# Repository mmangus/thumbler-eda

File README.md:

# thumbler-eda
EDA files for split keyboard with clicky encoder and thumb pointer

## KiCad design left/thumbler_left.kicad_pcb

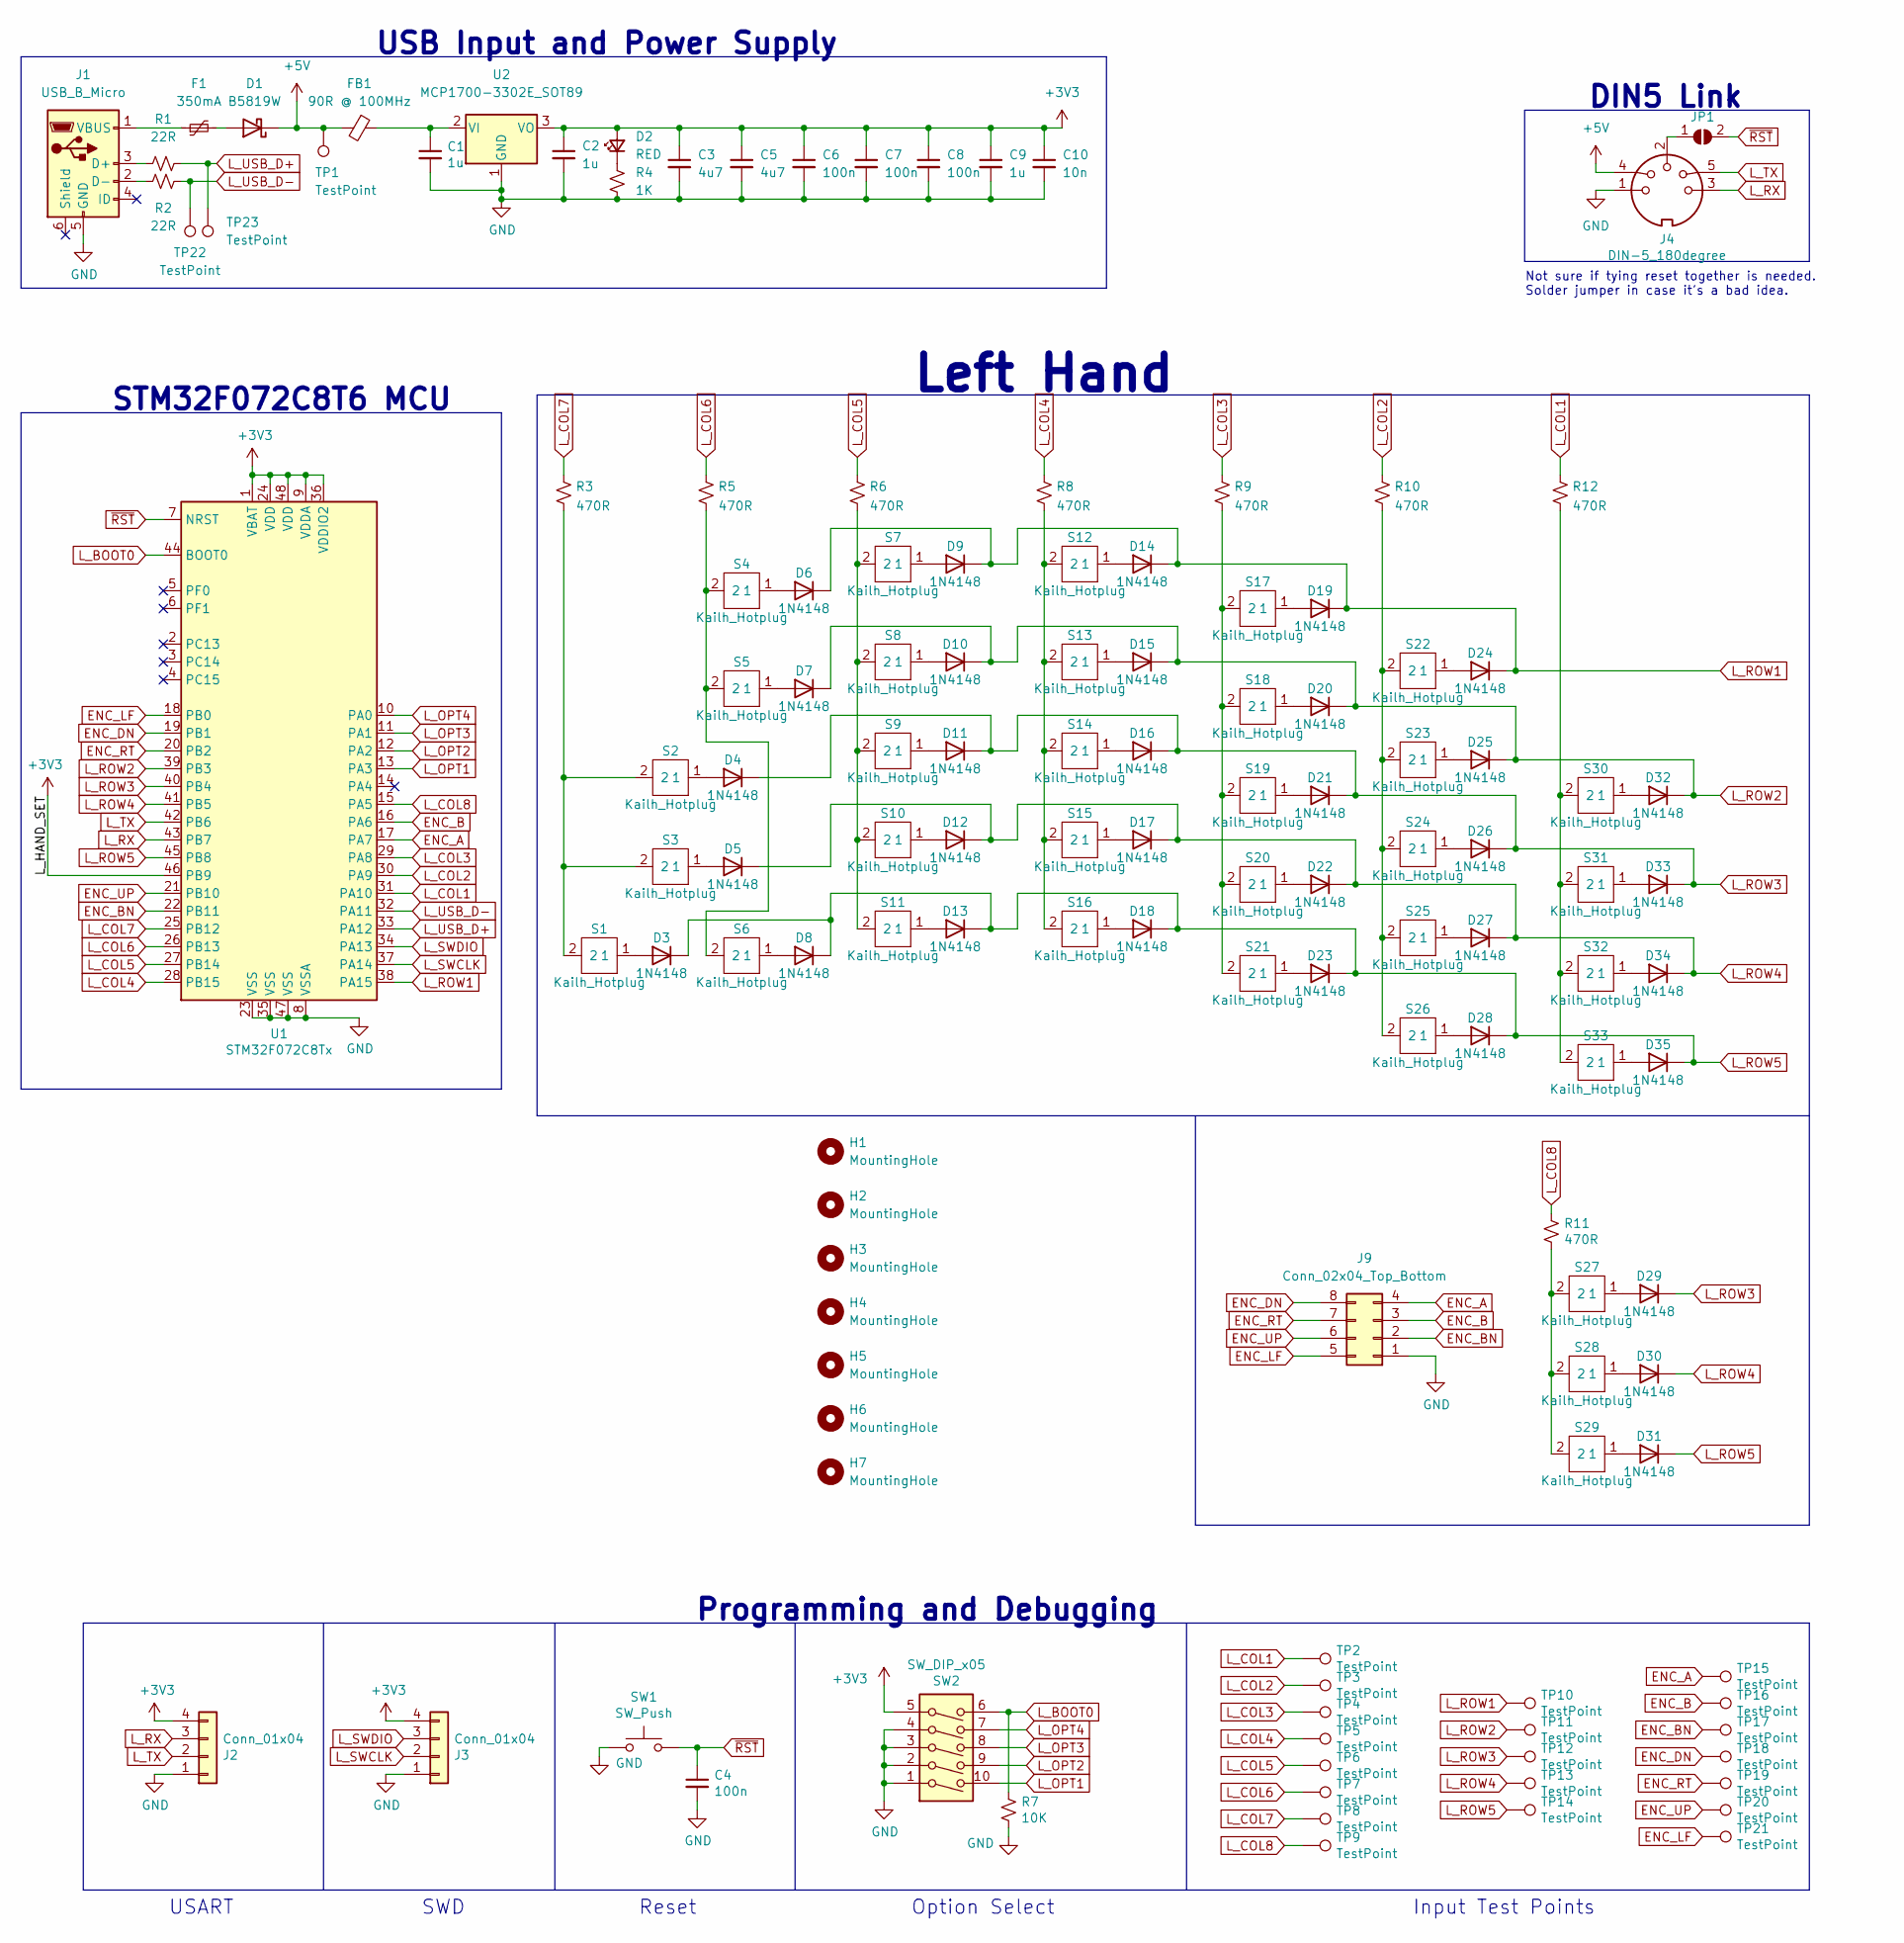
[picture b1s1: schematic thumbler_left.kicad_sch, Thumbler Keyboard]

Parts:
C1, C2: 1u; C_0805_2012Metric_Pad1.18x1.45mm_HandSolder
C3, C5: 4u7; C_0603_1608Metric_Pad1.08x0.95mm_HandSolder
C4: 100n; C_0805_2012Metric_Pad1.18x1.45mm_HandSolder
C6, C7, C8: 100n; C_0603_1608Metric_Pad1.08x0.95mm_HandSolder
C9: 1u; C_0603_1608Metric_Pad1.08x0.95mm_HandSolder
C10: 10n; C_0603_1608Metric_Pad1.08x0.95mm_HandSolder
D1: B5819W; D_SOD-123
D2: RED; LED_1206_3216Metric_Pad1.42x1.75mm_HandSolder
D3, D4, D5, D6, D7, D8, D9, D10, D11, D12, D13, D14, D15, D16, D17, D18, D19, D20, D21, D22, D23, D24, D25, D26, D27, D28, D29, D30, D31, D32, D33, D34, D35: 1N4148; D_DO-35_SOD27_P7.62mm_Horizontal
F1: 350mA; R_1812_4532Metric_Pad1.30x3.40mm_HandSolder
FB1: 90R @ 100MHz; L_0805_2012Metric_Pad1.15x1.40mm_HandSolder
H1, H2, H3, H4, H5, H6, H7: MountingHole; MountingHole_3.2mm_M3
J1: USB_B_Micro; USB_Micro-B_HRO_U-F-M5SS-W-1
J2, J3: Conn_01x04; PinHeader_2x02_P2.54mm_Vertical
J4: DIN-5_180degree; DIN5_180_CP-2350
J9: Conn_02x04_Top_Bottom; PinHeader_2x04_P2.54mm_Vertical
JP1: SolderJumper_2_Open; SolderJumper-2_P1.3mm_Open_TrianglePad1.0x1.5mm
R1, R2: 22R; R_0805_2012Metric_Pad1.20x1.40mm_HandSolder
R3, R5, R6, R8, R9, R10, R11, R12: 470R; R_0805_2012Metric_Pad1.20x1.40mm_HandSolder
R4: 1K; R_0805_2012Metric_Pad1.20x1.40mm_HandSolder
R7: 10K; R_0805_2012Metric_Pad1.20x1.40mm_HandSolder
S1, S2, S3, S4, S5, S6, S7, S8, S9, S10, S11, S12, S13, S14, S15, S16, S17, S18, S19, S20, S21, S22, S23, S24, S25, S26, S27, S28, S29, S30, S31, S32, S33: Kailh_Hotplug; Kailh_socket_MX_platemount
SW1: SW_Push; SW_PUSH-12mm
SW2: SW_DIP_x05; SW_DIP_SPSTx05_Slide_9.78x14.88mm_W7.62mm_P2.54mm
TP1, TP2, TP3, TP4, TP5, TP6, TP7, TP8, TP9, TP10, TP11, TP12, TP13, TP14, TP15, TP16, TP17, TP18, TP19, TP20, TP21, TP22, TP23: TestPoint; TestPoint_Pad_D2.0mm
U1: STM32F072C8Tx; LQFP-48_7x7mm_P0.5mm
U2: MCP1700-3302E_SOT89; SOT-89-3

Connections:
+3V3: C2.1, C3.1, C5.1, C6.1, C7.1, C8.1, C9.1, C10.1, D2.2 (A), J2.4, J3.4, SW2.5, U1.1 (VBAT), U1.9 (VDDA), U1.24 (VDD), U1.36 (VDDIO2), U1.46 (PB9), U1.48 (VDD), U2.3 (VO)
+5V: D1.1 (K), FB1.2, J4.4, TP1.1
ENC_A: J9.4, TP15.1, U1.17 (PA7)
ENC_B: J9.3, TP16.1, U1.16 (PA6)
ENC_BN: J9.2, TP17.1, U1.22 (PB11)
ENC_DN: J9.8, TP18.1, U1.19 (PB1)
ENC_LF: J9.5, TP21.1, U1.18 (PB0)
ENC_RT: J9.7, TP19.1, U1.20 (PB2)
ENC_UP: J9.6, TP20.1, U1.21 (PB10)
GND: C1.2, C2.2, C3.2, C4.2, C5.2, C6.2, C7.2, C8.2, C9.2, C10.2, J1.5 (GND), J2.1, J3.1, J4.1, J9.1, R4.2, R7.2, SW1.1, SW2.1, SW2.2, SW2.3, SW2.4, U1.8 (VSSA), U1.23 (VSS), U1.35 (VSS), U1.47 (VSS), U2.1 (GND)
L_BOOT0: R7.1, SW2.6, U1.44 (BOOT0)
L_COL1: R12.1, TP2.1, U1.31 (PA10)
L_COL2: R10.1, TP3.1, U1.30 (PA9)
L_COL3: R9.1, TP4.1, U1.29 (PA8)
L_COL4: R8.1, TP5.1, U1.28 (PB15)
L_COL5: R6.1, TP6.1, U1.27 (PB14)
L_COL6: R5.1, TP7.1, U1.26 (PB13)
L_COL7: R3.1, TP8.1, U1.25 (PB12)
L_COL8: R11.1, TP9.1, U1.15 (PA5)
L_OPT1: SW2.10, U1.13 (PA3)
L_OPT2: SW2.9, U1.12 (PA2)
L_OPT3: SW2.8, U1.11 (PA1)
L_OPT4: SW2.7, U1.10 (PA0)
L_ROW1: D6.1 (K), D9.1 (K), D14.1 (K), D19.1 (K), D24.1 (K), TP10.1, U1.38 (PA15)
L_ROW2: D7.1 (K), D10.1 (K), D15.1 (K), D20.1 (K), D25.1 (K), D32.1 (K), TP11.1, U1.39 (PB3)
L_ROW3: D4.1 (K), D11.1 (K), D16.1 (K), D21.1 (K), D26.1 (K), D29.1 (K), D33.1 (K), TP12.1, U1.40 (PB4)
L_ROW4: D5.1 (K), D12.1 (K), D17.1 (K), D22.1 (K), D27.1 (K), D30.1 (K), D34.1 (K), TP13.1, U1.41 (PB5)
L_ROW5: D3.1 (K), D8.1 (K), D13.1 (K), D18.1 (K), D23.1 (K), D28.1 (K), D31.1 (K), D35.1 (K), TP14.1, U1.45 (PB8)
L_RX: J2.3, J4.3, U1.43 (PB7)
L_SWCLK: J3.2, U1.37 (PA14)
L_SWDIO: J3.3, U1.34 (PA13)
L_TX: J2.2, J4.5, U1.42 (PB6)
L_USB_D+: R1.1, TP23.1, U1.33 (PA12)
L_USB_D-: R2.2, TP22.1, U1.32 (PA11)
unnamed: C1.1, FB1.1, U2.2 (VI)
unnamed: D1.2 (A), F1.2
unnamed: D2.1 (K), R4.1
unnamed: D3.2 (A), S1.1
unnamed: D4.2 (A), S2.1
unnamed: D5.2 (A), S3.1
unnamed: D6.2 (A), S4.1
unnamed: D7.2 (A), S5.1
unnamed: D8.2 (A), S6.1
unnamed: D9.2 (A), S7.1
unnamed: D10.2 (A), S8.1
unnamed: D11.2 (A), S9.1
unnamed: D12.2 (A), S10.1
unnamed: D13.2 (A), S11.1
unnamed: D14.2 (A), S12.1
unnamed: D15.2 (A), S13.1
unnamed: D16.2 (A), S14.1
unnamed: D17.2 (A), S15.1
unnamed: D18.2 (A), S16.1
unnamed: D19.2 (A), S17.1
unnamed: D20.2 (A), S18.1
unnamed: D21.2 (A), S19.1
unnamed: D22.2 (A), S20.1
unnamed: D23.2 (A), S21.1
unnamed: D24.2 (A), S22.1
unnamed: D25.2 (A), S23.1
unnamed: D26.2 (A), S24.1
unnamed: D27.2 (A), S25.1
unnamed: D28.2 (A), S26.1
unnamed: D29.2 (A), S27.1
unnamed: D30.2 (A), S28.1
unnamed: D31.2 (A), S29.1
unnamed: D32.2 (A), S30.1
unnamed: D33.2 (A), S31.1
unnamed: D34.2 (A), S32.1
unnamed: D35.2 (A), S33.1
unnamed: F1.1, J1.1 (VBUS)
unnamed: J1.2 (D-), R2.1
unnamed: J1.3 (D+), R1.2
unnamed: J4.2, JP1.1 (A)
unnamed: R3.2, S1.2, S2.2, S3.2
unnamed: R5.2, S4.2, S5.2, S6.2
unnamed: R6.2, S7.2, S8.2, S9.2, S10.2, S11.2
unnamed: R8.2, S12.2, S13.2, S14.2, S15.2, S16.2
unnamed: R9.2, S17.2, S18.2, S19.2, S20.2, S21.2
unnamed: R10.2, S22.2, S23.2, S24.2, S25.2, S26.2
unnamed: R11.2, S27.2, S28.2, S29.2
unnamed: R12.2, S30.2, S31.2, S32.2, S33.2
~RST: C4.1, JP1.2 (B), SW1.2, U1.7 (NRST)

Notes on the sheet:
Option Select
Reset
Programming and Debugging
USB Input and Power Supply
DIN5 Link
USART
STM32F072C8T6 MCU
SWD
Not sure if tying reset together is needed. Solder jumper in case it's a bad idea.
Input Test Points
Left Hand

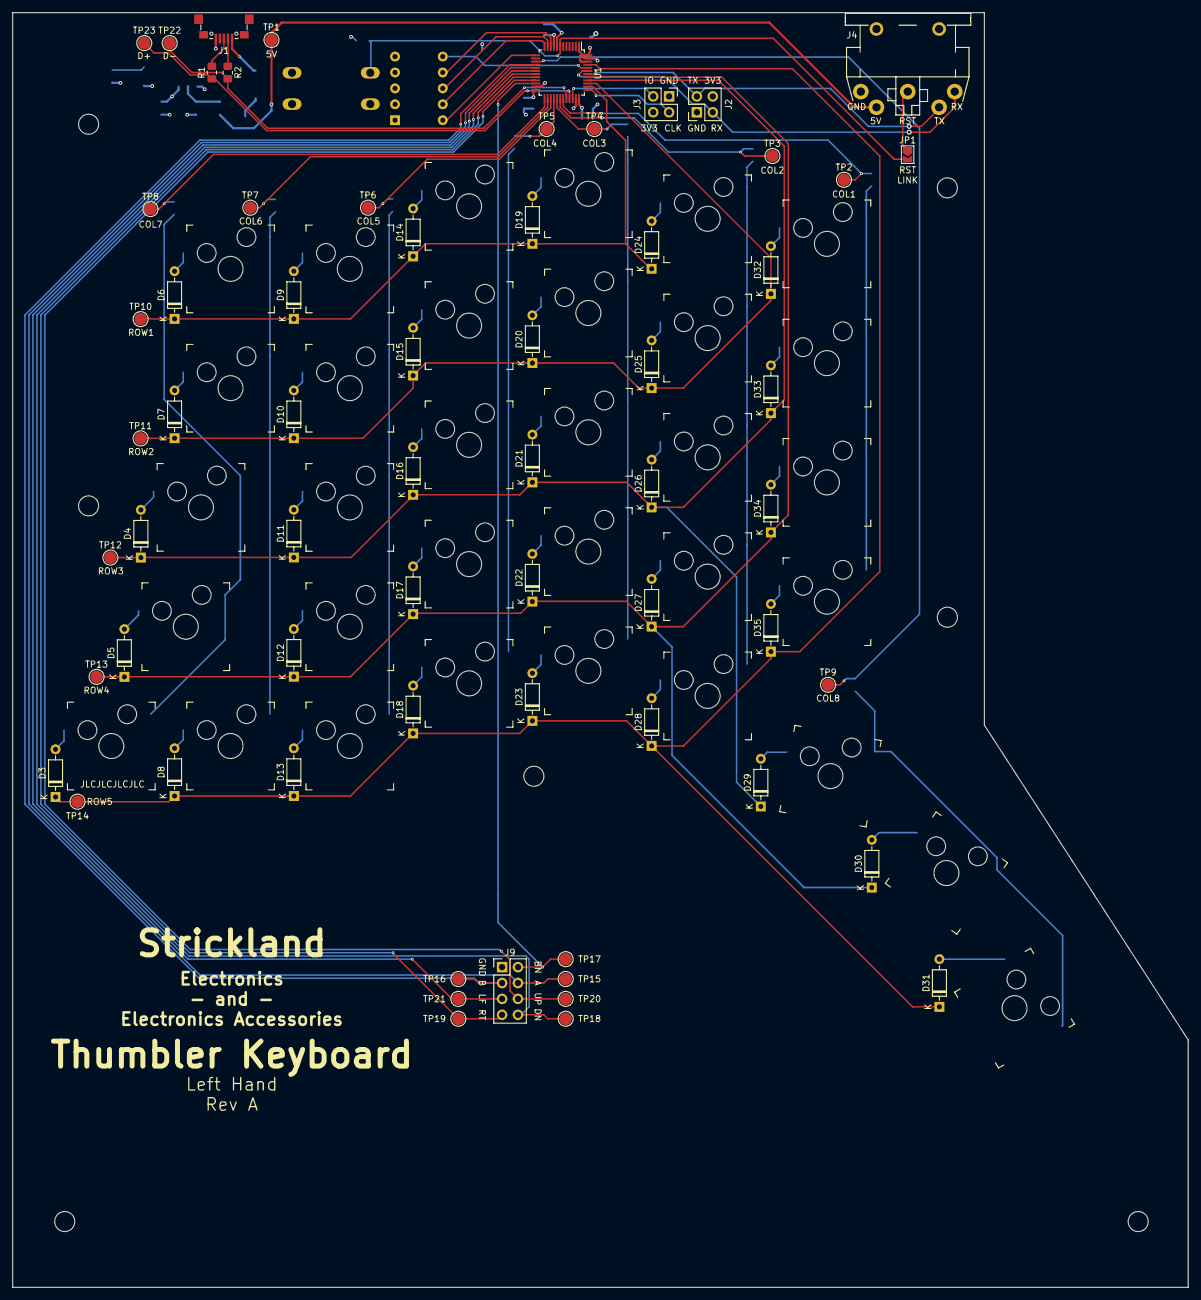
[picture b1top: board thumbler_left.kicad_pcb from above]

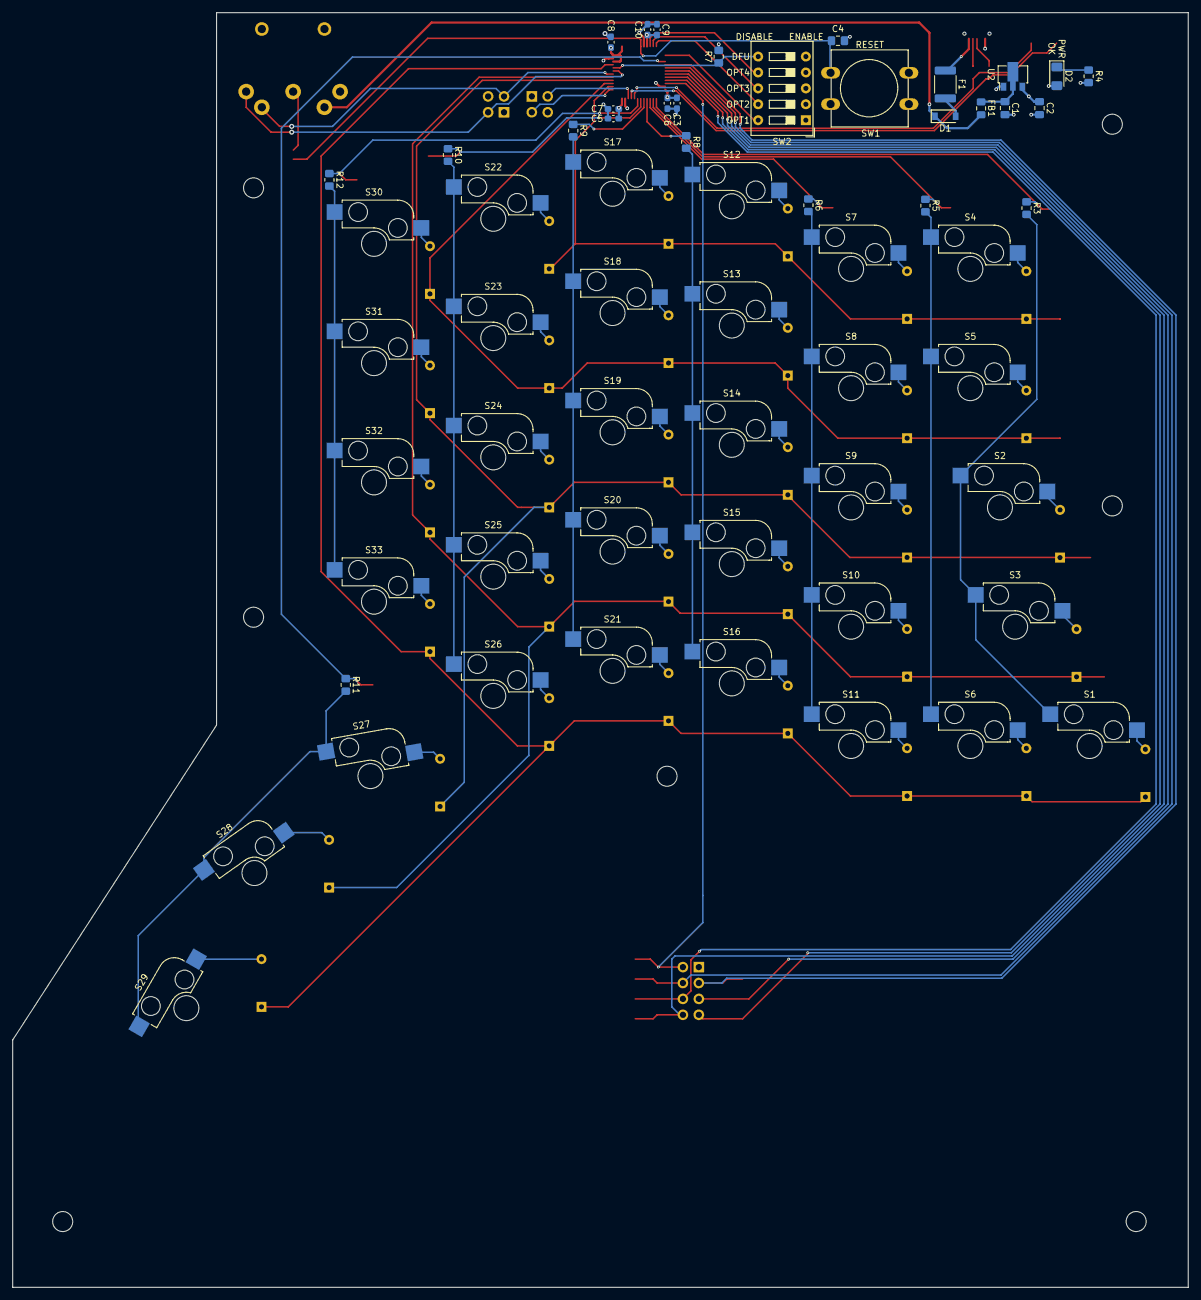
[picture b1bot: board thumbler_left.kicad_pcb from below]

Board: 4 copper layers, 187.8 x 203.6 mm, 132 parts (27 on the bottom side), 83 nets.

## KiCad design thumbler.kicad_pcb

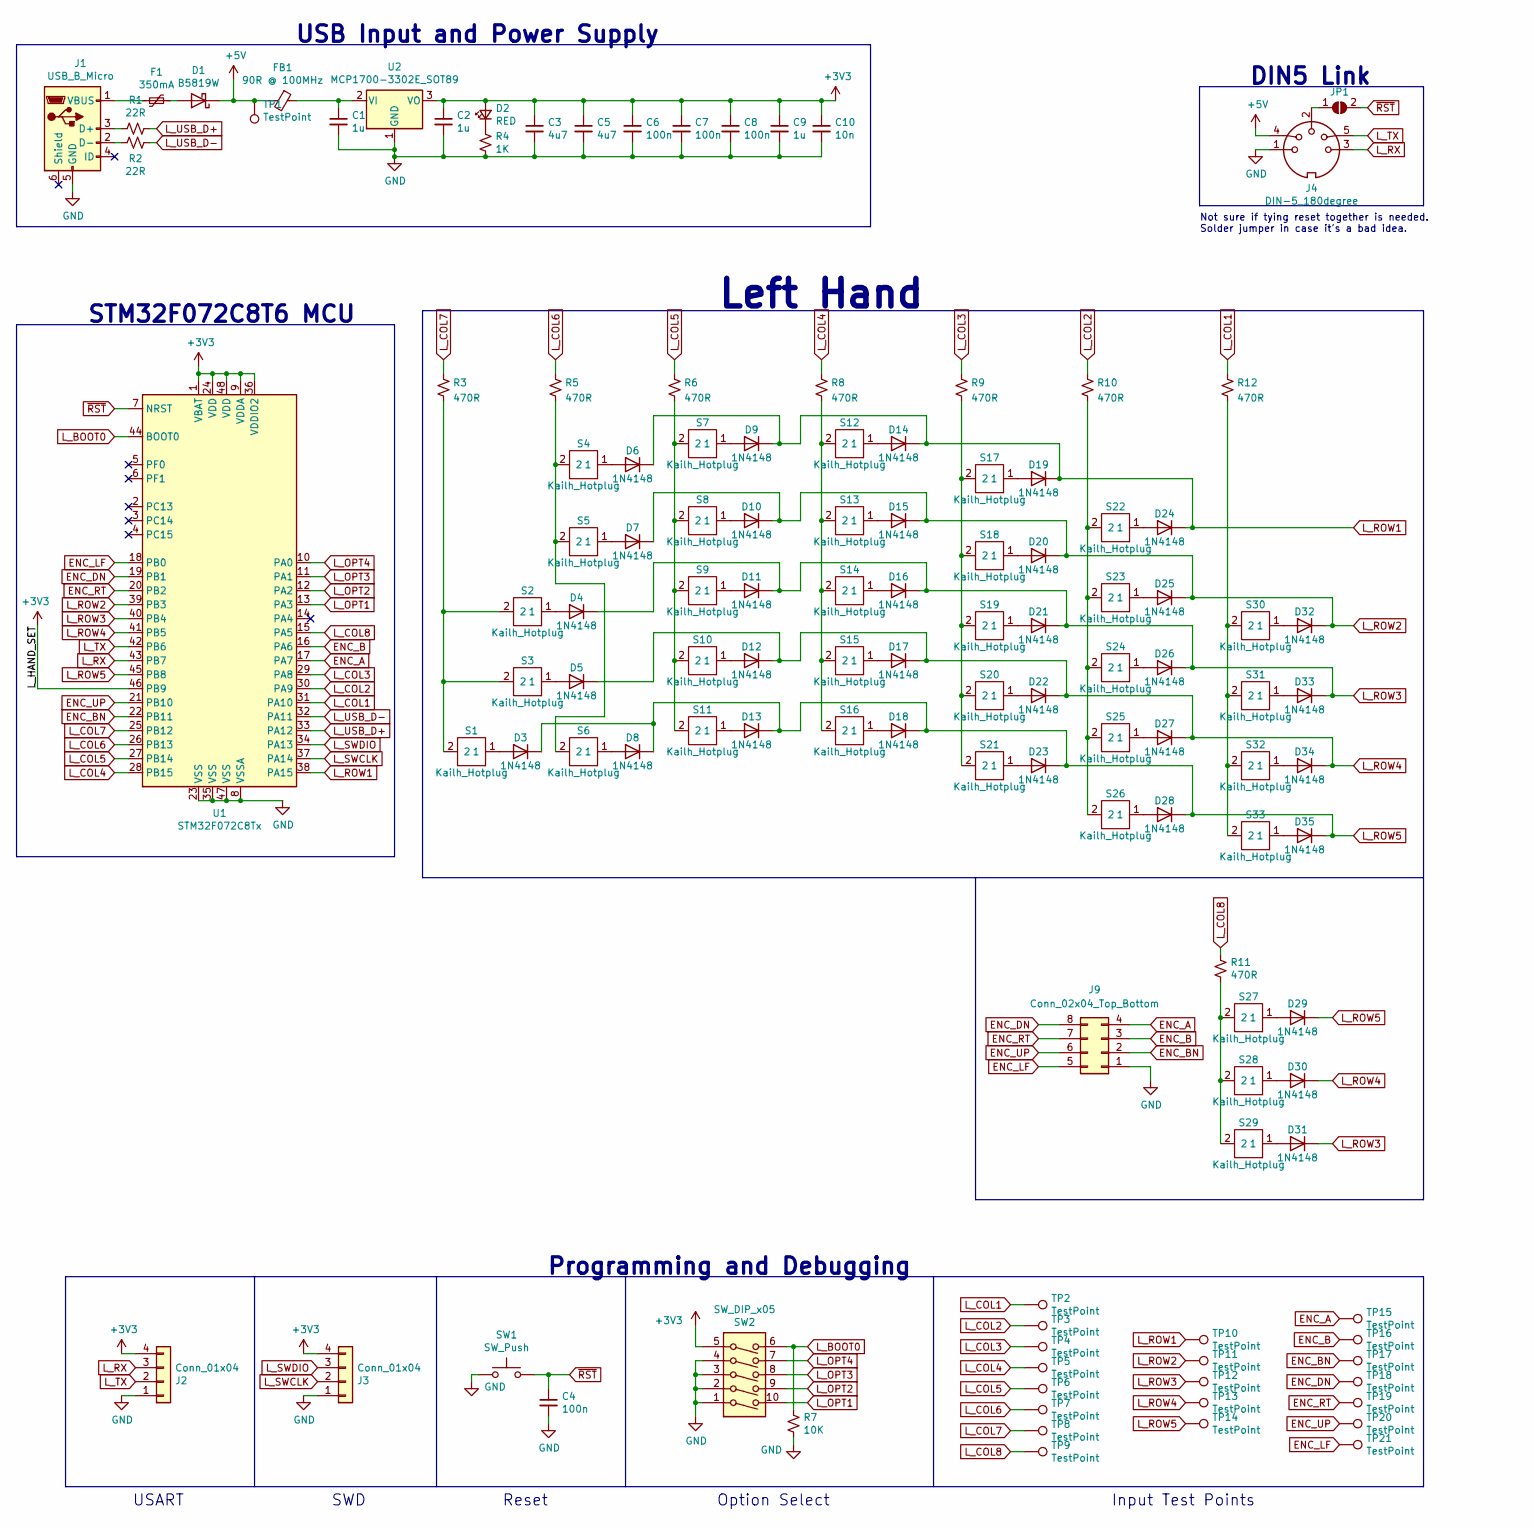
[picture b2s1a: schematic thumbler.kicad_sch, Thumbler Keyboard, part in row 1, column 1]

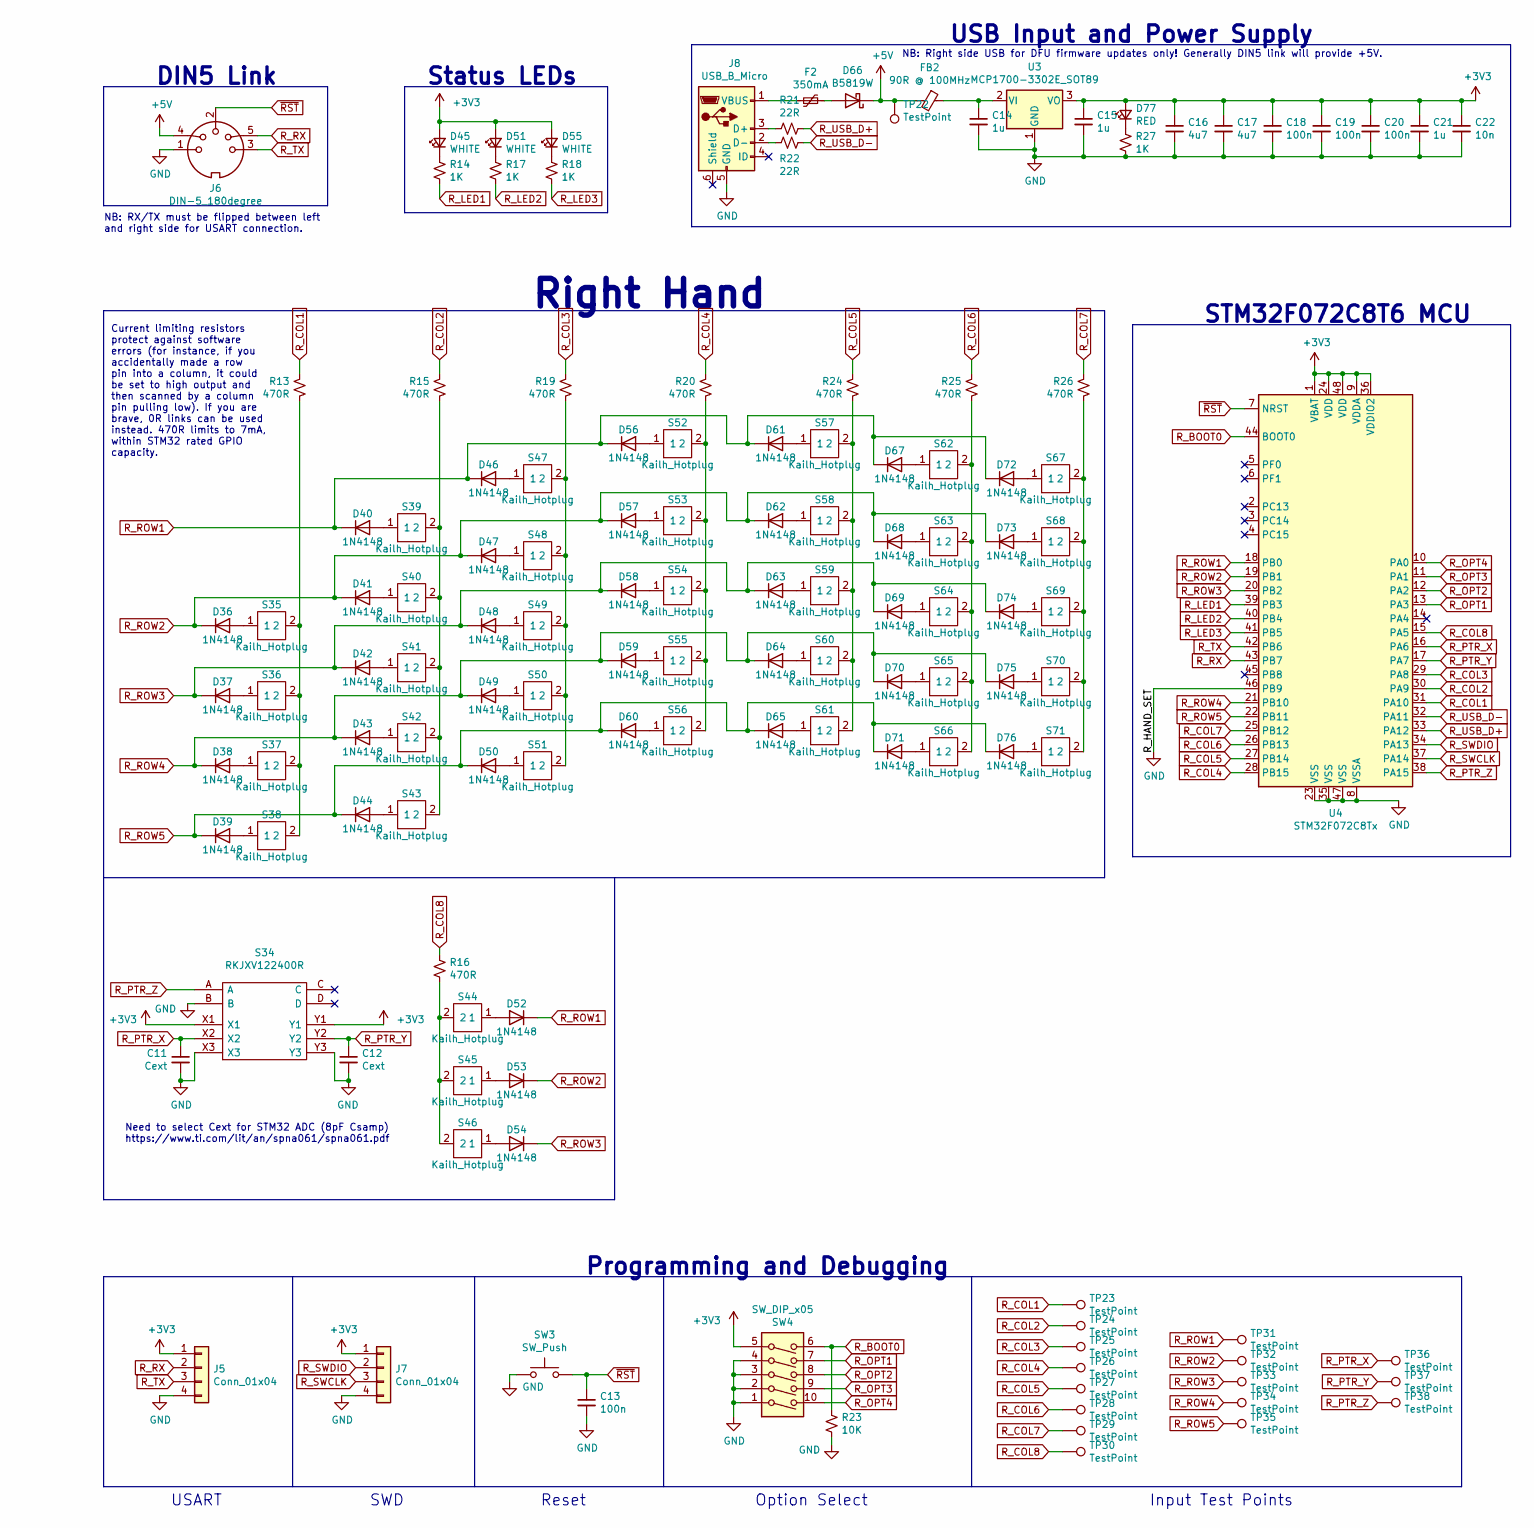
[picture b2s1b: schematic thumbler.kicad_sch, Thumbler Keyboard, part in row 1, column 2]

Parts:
C1, C2, C14, C15: 1u; C_0805_2012Metric_Pad1.18x1.45mm_HandSolder
C3, C5, C16, C17: 4u7; C_0603_1608Metric_Pad1.08x0.95mm_HandSolder
C4, C13: 100n; C_0805_2012Metric_Pad1.18x1.45mm_HandSolder
C6, C7, C8, C18, C19, C20: 100n; C_0603_1608Metric_Pad1.08x0.95mm_HandSolder
C9, C21: 1u; C_0603_1608Metric_Pad1.08x0.95mm_HandSolder
C10, C22: 10n; C_0603_1608Metric_Pad1.08x0.95mm_HandSolder
C11, C12: Cext; C_0805_2012Metric_Pad1.18x1.45mm_HandSolder
D1, D66: B5819W; D_SOD-123
D2, D77: RED; LED_1206_3216Metric_Pad1.42x1.75mm_HandSolder
D3, D4, D5, D6, D7, D8, D9, D10, D11, D12, D13, D14, D15, D16, D17, D18, D19, D20, D21, D22, D23, D24, D25, D26, D27, D28, D29, D30, D31, D32, D33, D34, D35, D36, D37, D38, D39, D40, D41, D42, D43, D44, D46, D47, D48, D49, D50, D52, D53, D54, D56, D57, D58, D59, D60, D61, D62, D63, D64, D65, D67, D68, D69, D70, D71, D72, D73, D74, D75, D76: 1N4148; D_DO-35_SOD27_P7.62mm_Horizontal
D45, D51, D55: WHITE; LED_1206_3216Metric_Pad1.42x1.75mm_HandSolder
F1, F2: 350mA; R_1812_4532Metric_Pad1.30x3.40mm_HandSolder
FB1, FB2: 90R @ 100MHz; L_0805_2012Metric_Pad1.15x1.40mm_HandSolder
J1, J8: USB_B_Micro; USB_Micro-B_HRO_U-F-M5SS-W-1
J2, J3, J5, J7: Conn_01x04; PinHeader_2x02_P2.54mm_Vertical
J4, J6: DIN-5_180degree; DIN5_180_CP-2350
J9: Conn_02x04_Top_Bottom; PinHeader_2x04_P2.54mm_Vertical
JP1: SolderJumper_2_Open; SolderJumper-2_P1.3mm_Open_TrianglePad1.0x1.5mm
R1, R2, R21, R22: 22R; R_0805_2012Metric_Pad1.20x1.40mm_HandSolder
R3, R5, R6, R8, R9, R10, R11, R12, R13, R15, R16, R19, R20, R24, R25, R26: 470R; R_0805_2012Metric_Pad1.20x1.40mm_HandSolder
R4, R14, R17, R18, R27: 1K; R_0805_2012Metric_Pad1.20x1.40mm_HandSolder
R7, R23: 10K; R_0805_2012Metric_Pad1.20x1.40mm_HandSolder
S1, S2, S3, S4, S5, S6, S7, S8, S9, S10, S11, S12, S13, S14, S15, S16, S17, S18, S19, S20, S21, S22, S23, S24, S25, S26, S27, S28, S29, S30, S31, S32, S33, S35, S36, S37, S38, S39, S40, S41, S42, S43, S44, S45, S46, S47, S48, S49, S50, S51, S52, S53, S54, S55, S56, S57, S58, S59, S60, S61, S62, S63, S64, S65, S66, S67, S68, S69, S70, S71: Kailh_Hotplug; Kailh_socket_MX_platemount
S34: RKJXV122400R; Manufacturer_Part_Number RKJXV122400R; Mouser Part Number 688-RKJXV122400R
SW1, SW3: SW_Push; SW_PUSH-12mm
SW2, SW4: SW_DIP_x05; SW_DIP_SPSTx05_Slide_9.78x14.88mm_W7.62mm_P2.54mm
TP1, TP2, TP3, TP4, TP5, TP6, TP7, TP8, TP9, TP10, TP11, TP12, TP13, TP14, TP15, TP16, TP17, TP18, TP19, TP20, TP21, TP22, TP23, TP24, TP25, TP26, TP27, TP28, TP29, TP30, TP31, TP32, TP33, TP34, TP35, TP36, TP37, TP38: TestPoint; TestPoint_Pad_D2.0mm
U1, U4: STM32F072C8Tx; LQFP-48_7x7mm_P0.5mm
U2, U3: MCP1700-3302E_SOT89; SOT-89-3

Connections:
+3V3: C2.1, C3.1, C5.1, C6.1, C7.1, C8.1, C9.1, C10.1, C15.1, C16.1, C17.1, C18.1, C19.1, C20.1, C21.1, C22.1, D2.2 (A), D45.2 (A), D51.2 (A), D55.2 (A), D77.2 (A), J2.4, J3.4, J5.1, J7.1, S34.X1, S34.Y1, SW2.5, SW4.5, U1.1 (VBAT), U1.9 (VDDA), U1.24 (VDD), U1.36 (VDDIO2), U1.46 (PB9), U1.48 (VDD), U2.3 (VO), U3.3 (VO), U4.1 (VBAT), U4.9 (VDDA), U4.24 (VDD), U4.36 (VDDIO2), U4.48 (VDD)
+5V: D1.1 (K), D66.1 (K), FB1.2, FB2.2, J4.4, J6.4, TP1.1, TP22.1
ENC_A: J9.4, TP15.1, U1.17 (PA7)
ENC_B: J9.3, TP16.1, U1.16 (PA6)
ENC_BN: J9.2, TP17.1, U1.22 (PB11)
ENC_DN: J9.8, TP18.1, U1.19 (PB1)
ENC_LF: J9.5, TP21.1, U1.18 (PB0)
ENC_RT: J9.7, TP19.1, U1.20 (PB2)
ENC_UP: J9.6, TP20.1, U1.21 (PB10)
GND: C1.2, C2.2, C3.2, C4.2, C5.2, C6.2, C7.2, C8.2, C9.2, C10.2, C11.2, C12.2, C13.2, C14.2, C15.2, C16.2, C17.2, C18.2, C19.2, C20.2, C21.2, C22.2, J1.5 (GND), J2.1, J3.1, J4.1, J5.4, J6.1, J7.4, J8.5 (GND), J9.1, R4.2, R7.2, R23.2, R27.2, S34.B, S34.X3, S34.Y3, SW1.1, SW2.1, SW2.2, SW2.3, SW2.4, SW3.1, SW4.1, SW4.2, SW4.3, SW4.4, U1.8 (VSSA), U1.23 (VSS), U1.35 (VSS), U1.47 (VSS), U2.1 (GND), U3.1 (GND), U4.8 (VSSA), U4.23 (VSS), U4.35 (VSS), U4.46 (PB9), U4.47 (VSS)
L_BOOT0: R7.1, SW2.6, U1.44 (BOOT0)
L_COL1: R12.1, TP2.1, U1.31 (PA10)
L_COL2: R10.1, TP3.1, U1.30 (PA9)
L_COL3: R9.1, TP4.1, U1.29 (PA8)
L_COL4: R8.1, TP5.1, U1.28 (PB15)
L_COL5: R6.1, TP6.1, U1.27 (PB14)
L_COL6: R5.1, TP7.1, U1.26 (PB13)
L_COL7: R3.1, TP8.1, U1.25 (PB12)
L_COL8: R11.1, TP9.1, U1.15 (PA5)
L_OPT1: SW2.10, U1.13 (PA3)
L_OPT2: SW2.9, U1.12 (PA2)
L_OPT3: SW2.8, U1.11 (PA1)
L_OPT4: SW2.7, U1.10 (PA0)
L_ROW1: D6.1 (K), D9.1 (K), D14.1 (K), D19.1 (K), D24.1 (K), TP10.1, U1.38 (PA15)
L_ROW2: D7.1 (K), D10.1 (K), D15.1 (K), D20.1 (K), D25.1 (K), D32.1 (K), TP11.1, U1.39 (PB3)
L_ROW3: D4.1 (K), D11.1 (K), D16.1 (K), D21.1 (K), D26.1 (K), D31.1 (K), D33.1 (K), TP12.1, U1.40 (PB4)
L_ROW4: D5.1 (K), D12.1 (K), D17.1 (K), D22.1 (K), D27.1 (K), D30.1 (K), D34.1 (K), TP13.1, U1.41 (PB5)
L_ROW5: D3.1 (K), D8.1 (K), D13.1 (K), D18.1 (K), D23.1 (K), D28.1 (K), D29.1 (K), D35.1 (K), TP14.1, U1.45 (PB8)
L_RX: J2.3, J4.3, U1.43 (PB7)
L_SWCLK: J3.2, U1.37 (PA14)
L_SWDIO: J3.3, U1.34 (PA13)
L_TX: J2.2, J4.5, U1.42 (PB6)
L_USB_D+: R1.1, U1.33 (PA12)
L_USB_D-: R2.2, U1.32 (PA11)
unnamed: C1.1, FB1.1, U2.2 (VI)
unnamed: C14.1, FB2.1, U3.2 (VI)
unnamed: D1.2 (A), F1.2
unnamed: D2.1 (K), R4.1
unnamed: D3.2 (A), S1.1
unnamed: D4.2 (A), S2.1
unnamed: D5.2 (A), S3.1
unnamed: D6.2 (A), S4.1
unnamed: D7.2 (A), S5.1
unnamed: D8.2 (A), S6.1
unnamed: D9.2 (A), S7.1
unnamed: D10.2 (A), S8.1
unnamed: D11.2 (A), S9.1
unnamed: D12.2 (A), S10.1
unnamed: D13.2 (A), S11.1
unnamed: D14.2 (A), S12.1
unnamed: D15.2 (A), S13.1
unnamed: D16.2 (A), S14.1
unnamed: D17.2 (A), S15.1
unnamed: D18.2 (A), S16.1
unnamed: D19.2 (A), S17.1
unnamed: D20.2 (A), S18.1
unnamed: D21.2 (A), S19.1
unnamed: D22.2 (A), S20.1
unnamed: D23.2 (A), S21.1
unnamed: D24.2 (A), S22.1
unnamed: D25.2 (A), S23.1
unnamed: D26.2 (A), S24.1
unnamed: D27.2 (A), S25.1
unnamed: D28.2 (A), S26.1
unnamed: D29.2 (A), S27.1
unnamed: D30.2 (A), S28.1
unnamed: D31.2 (A), S29.1
unnamed: D32.2 (A), S30.1
unnamed: D33.2 (A), S31.1
unnamed: D34.2 (A), S32.1
unnamed: D35.2 (A), S33.1
unnamed: D36.2 (A), S35.1
unnamed: D37.2 (A), S36.1
unnamed: D38.2 (A), S37.1
unnamed: D39.2 (A), S38.1
unnamed: D40.2 (A), S39.1
unnamed: D41.2 (A), S40.1
unnamed: D42.2 (A), S41.1
unnamed: D43.2 (A), S42.1
unnamed: D44.2 (A), S43.1
unnamed: D45.1 (K), R14.1
unnamed: D46.2 (A), S47.1
unnamed: D47.2 (A), S48.1
unnamed: D48.2 (A), S49.1
unnamed: D49.2 (A), S50.1
unnamed: D50.2 (A), S51.1
unnamed: D51.1 (K), R17.1
unnamed: D52.2 (A), S44.1
unnamed: D53.2 (A), S45.1
unnamed: D54.2 (A), S46.1
unnamed: D55.1 (K), R18.1
unnamed: D56.2 (A), S52.1
unnamed: D57.2 (A), S53.1
unnamed: D58.2 (A), S54.1
unnamed: D59.2 (A), S55.1
unnamed: D60.2 (A), S56.1
unnamed: D61.2 (A), S57.1
unnamed: D62.2 (A), S58.1
unnamed: D63.2 (A), S59.1
unnamed: D64.2 (A), S60.1
unnamed: D65.2 (A), S61.1
unnamed: D66.2 (A), F2.2
unnamed: D67.2 (A), S62.1
unnamed: D68.2 (A), S63.1
unnamed: D69.2 (A), S64.1
unnamed: D70.2 (A), S65.1
unnamed: D71.2 (A), S66.1
unnamed: D72.2 (A), S67.1
unnamed: D73.2 (A), S68.1
unnamed: D74.2 (A), S69.1
unnamed: D75.2 (A), S70.1
unnamed: D76.2 (A), S71.1
unnamed: D77.1 (K), R27.1
unnamed: F1.1, J1.1 (VBUS)
unnamed: F2.1, J8.1 (VBUS)
unnamed: J1.2 (D-), R2.1
unnamed: J1.3 (D+), R1.2
unnamed: J4.2, JP1.1 (A)
unnamed: J8.2 (D-), R22.1
unnamed: J8.3 (D+), R21.2
unnamed: R3.2, S1.2, S2.2, S3.2
unnamed: R5.2, S4.2, S5.2, S6.2
unnamed: R6.2, S7.2, S8.2, S9.2, S10.2, S11.2
unnamed: R8.2, S12.2, S13.2, S14.2, S15.2, S16.2
unnamed: R9.2, S17.2, S18.2, S19.2, S20.2, S21.2
unnamed: R10.2, S22.2, S23.2, S24.2, S25.2, S26.2
unnamed: R11.2, S27.2, S28.2, S29.2
unnamed: R12.2, S30.2, S31.2, S32.2, S33.2
unnamed: R13.2, S35.2, S36.2, S37.2, S38.2
unnamed: R15.2, S39.2, S40.2, S41.2, S42.2, S43.2
unnamed: R16.2, S44.2, S45.2, S46.2
unnamed: R19.2, S47.2, S48.2, S49.2, S50.2, S51.2
unnamed: R20.2, S52.2, S53.2, S54.2, S55.2, S56.2
unnamed: R24.2, S57.2, S58.2, S59.2, S60.2, S61.2
unnamed: R25.2, S62.2, S63.2, S64.2, S65.2, S66.2
unnamed: R26.2, S67.2, S68.2, S69.2, S70.2, S71.2
R_BOOT0: R23.1, SW4.6, U4.44 (BOOT0)
R_COL1: R13.1, TP23.1, U4.31 (PA10)
R_COL2: R15.1, TP24.1, U4.30 (PA9)
R_COL3: R19.1, TP25.1, U4.29 (PA8)
R_COL4: R20.1, TP26.1, U4.28 (PB15)
R_COL5: R24.1, TP27.1, U4.27 (PB14)
R_COL6: R25.1, TP28.1, U4.26 (PB13)
R_COL7: R26.1, TP29.1, U4.25 (PB12)
R_COL8: R16.1, TP30.1, U4.15 (PA5)
R_LED1: R14.2, U4.39 (PB3)
R_LED2: R17.2, U4.40 (PB4)
R_LED3: R18.2, U4.41 (PB5)
R_OPT1: SW4.7, U4.13 (PA3)
R_OPT2: SW4.8, U4.12 (PA2)
R_OPT3: SW4.9, U4.11 (PA1)
R_OPT4: SW4.10, U4.10 (PA0)
R_PTR_X: C11.1, S34.X2, TP36.1, U4.16 (PA6)
R_PTR_Y: C12.1, S34.Y2, TP37.1, U4.17 (PA7)
R_PTR_Z: S34.A, TP38.1, U4.38 (PA15)
R_ROW1: D40.1 (K), D46.1 (K), D52.1 (K), D56.1 (K), D61.1 (K), D67.1 (K), D72.1 (K), TP31.1, U4.18 (PB0)
R_ROW2: D36.1 (K), D41.1 (K), D47.1 (K), D53.1 (K), D57.1 (K), D62.1 (K), D68.1 (K), D73.1 (K), TP32.1, U4.19 (PB1)
R_ROW3: D37.1 (K), D42.1 (K), D48.1 (K), D54.1 (K), D58.1 (K), D63.1 (K), D69.1 (K), D74.1 (K), TP33.1, U4.20 (PB2)
R_ROW4: D38.1 (K), D43.1 (K), D49.1 (K), D59.1 (K), D64.1 (K), D70.1 (K), D75.1 (K), TP34.1, U4.21 (PB10)
R_ROW5: D39.1 (K), D44.1 (K), D50.1 (K), D60.1 (K), D65.1 (K), D71.1 (K), D76.1 (K), TP35.1, U4.22 (PB11)
R_RX: J5.2, J6.5, U4.43 (PB7)
R_SWCLK: J7.3, U4.37 (PA14)
R_SWDIO: J7.2, U4.34 (PA13)
R_TX: J5.3, J6.3, U4.42 (PB6)
R_USB_D+: R21.1, U4.33 (PA12)
R_USB_D-: R22.2, U4.32 (PA11)
~RST: C4.1, C13.1, J6.2, JP1.2 (B), SW1.2, SW3.2, U1.7 (NRST), U4.7 (NRST)

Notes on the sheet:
Reset
Option Select
NB: Right side USB for DFU firmware updates only! Generally DIN5 link will provide +5V.
USART
Programming and Debugging
Status LEDs
USB Input and Power Supply
DIN5 Link
Current limiting resistors protect against software errors (for instance, if you accidentally made a row pin into a column, it could be set to high output and then scanned by a column pin pulling low). If you are brave, 0R links can be used instead. 470R limits to 7mA, within STM32 rated GPIO capac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
Need to select Cext for STM32 ADC (8pF Csamp) https://www.ti.com/lit/an/spna061/spna061.pdf
STM32F072C8T6 MCU
SWD
NB: RX/TX must be flipped between left and right side for USART connection.
Input Test Points
Right Hand
Not sure if tying reset together is needed. Solder jumper in case it's a bad idea.
Left Hand

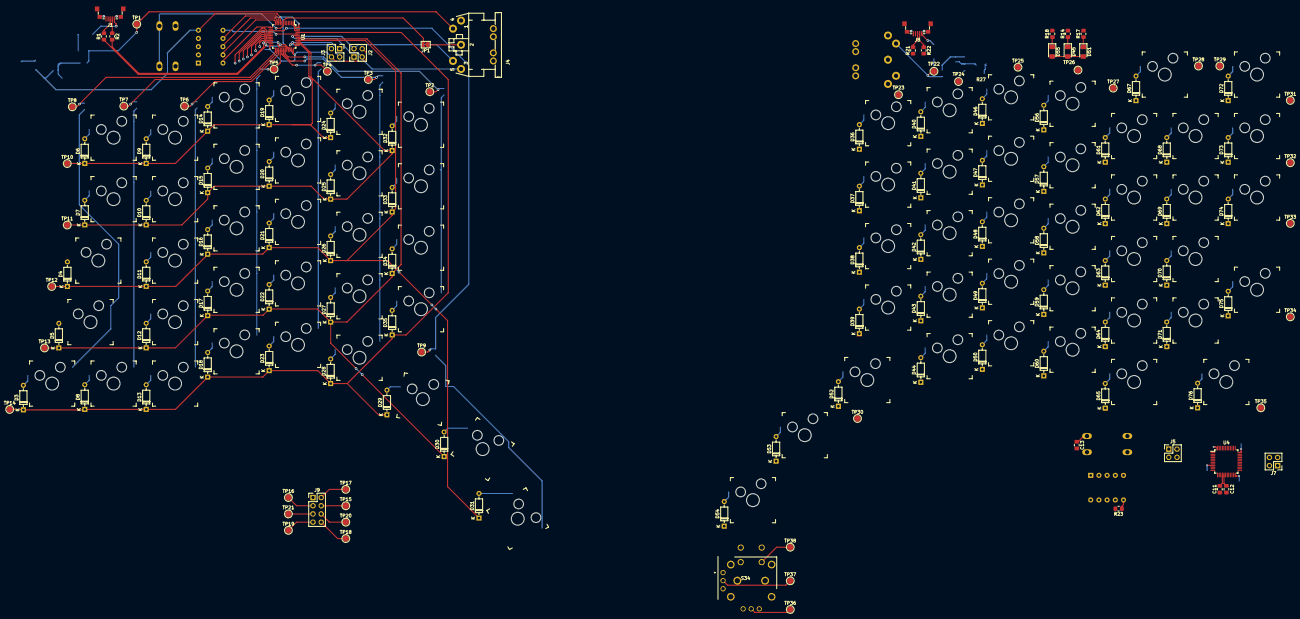
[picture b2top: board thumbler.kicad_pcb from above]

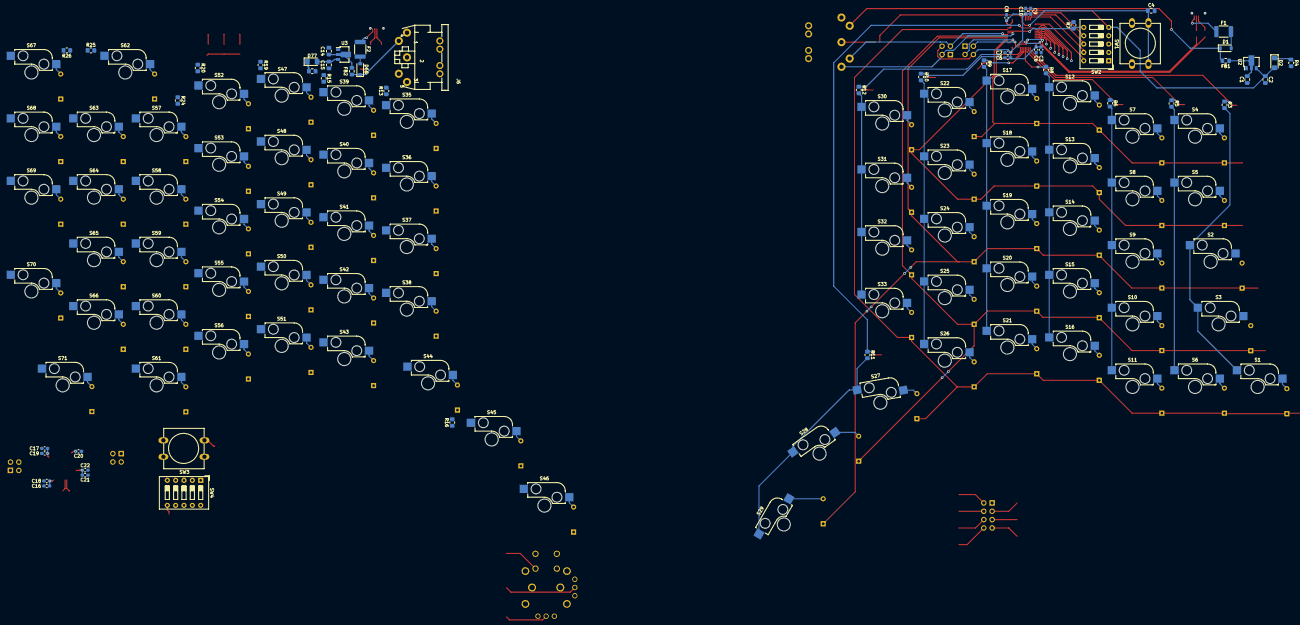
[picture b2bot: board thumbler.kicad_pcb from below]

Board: 2 copper layers, 257 parts (53 on the bottom side), 167 nets.

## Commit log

2021-11-27 add current limiting resistors to USB D+/-
2021-11-29 thumb v0, options, optimizations
2021-11-30 add footprint for ANO
2021-11-30 might need this too?
2021-12-04 more protection, more footprints
2021-12-05 footprints done
2021-12-06 layout wip
2021-12-13 left side re-layout mostly done
2021-12-13 revised layout basically done, minus thumbs
2021-12-13 fix right enter placement; still need to reannotate
2021-12-13 minor tidying
2021-12-26 70 key laid out
2021-12-26 all TPs to front
2021-12-26 test points and current-limiting resistors placed
2021-12-31 left mostly routed; kicad 6; need to cleanup files...
2021-12-31 more routing
2022-01-01 staritng to split files
2022-01-01 silkscreen
2022-01-01 tweak mounting holes
2022-01-03 restructuring and getting close
2022-01-03 ready to manufacture?
2022-01-03 commit right side gerber
2022-01-03 jlc-ready zips
2022-01-03 dont commit backup files
2022-01-03 dont commit encoder breakout backups either
